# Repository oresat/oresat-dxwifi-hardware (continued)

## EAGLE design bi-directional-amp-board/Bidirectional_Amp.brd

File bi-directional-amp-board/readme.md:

Notes on the Bi-Directional DxWiFi (2.412 GHz) Amp PCB
========================================================

Our stackup is something like this:

 1.2 mil - 1 oz Copper
13.3 mil - Rogers RO4350B
 1.2 mil - 1 oz Copper
31.1 mil - FR4 (e.g., NP175)
 1.2 mil - 1 oz Copper
13.3 mil - Rogers RO4350B
 1.2 mil - 1 oz Copper
--------
62.5 mil - 1/16" standard board thickness

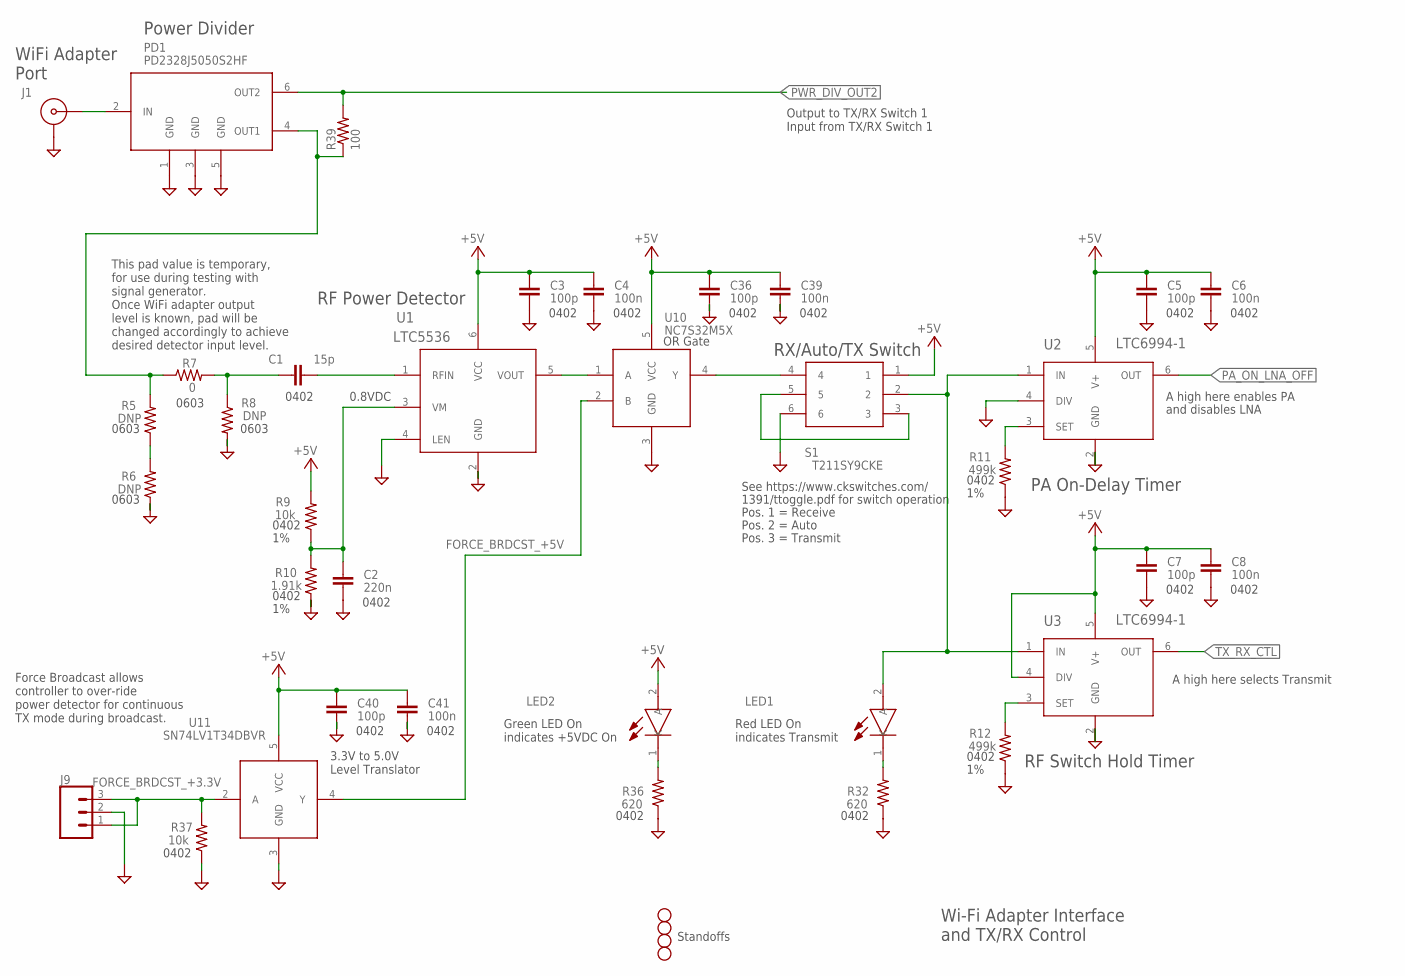
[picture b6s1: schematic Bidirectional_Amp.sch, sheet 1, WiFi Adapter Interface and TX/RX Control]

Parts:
C1: 15p; .0402-B-NOSILK; MPN GJM1555C1H150JB01D
C2: 220n; .0402-B-NOSILK; MPN C1005X7R1C224K050BE
C3, C5, C7, C36, C40: 100p; .0402-B-NOSILK; MPN GCM1555C1H101JA16D
C4, C6, C8, C39, C41: 100n; .0402-B-NOSILK; MPN CGA2B1X7R1C104K050BC
H1, H2, H3, H4: STAND-OFFTIGHT; STAND-OFF-TIGHT
J1: 73415-2061; 73415-2063; MPN 0734152061
J9: CONN_03LONGPADS; 1X03_LONGPADS
LED1: LTST-C193KRKT-5A; LEDC1607X80N
LED2: LTST-C193KGKT-5A; LEDC1607X80N
PD1: PD2328J5050S2HF; PSON65P204X129X58-6N
R5, R6, R8: DNP; R0603
R7: 0; R0603; MPN ERJ-3GEY0R00V
R9: 10k; .0402-B-NOSILK; MPN ERJ-2RKF1002X
R10: 1.91k; .0402-B-NOSILK; MPN ERJ-2RKF1911X
R11, R12: 499k; .0402-B-NOSILK; MPN ERJ-2RKF4993X
R32, R36: 620; .0402-B-NOSILK; MPN ERJ-2GEJ621X
R37: 10k; .0402-B-NOSILK; MPN ERJ-2GEJ103X
R39: 100; .0603-C-NOSILK; MPN ERJ-3EKF1000V
S1: T211SY9CKE; T201MH9V3BE
U1: LTC5536; TSOT-23_S6
U2, U3: LTC6994-1; TSOT-23_S6
U10: NC7S32M5X; SOT95P280X145-5N
U11: SN74LV1T34DBVR; SOT95P280X145-5N

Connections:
+5V: C3.1, C4.1, C5.1, C6.1, C7.1, C8.1, C36.1, C39.1, C40.1, C41.1, LED2.2 (A), R9.2, S1.1, U1.6 (VCC), U2.5 (V+), U3.4 (DIV), U3.5 (V+), U10.5 (VCC), U11.5 (VCC); also elsewhere on the board
FORCE_BRDCST_+3.3V: J9.1, J9.3, R37.2, U11.2 (A)
FORCE_BRDCST_+5V: U10.2 (B), U11.4 (Y)
GND: C2.2, C3.2, C4.2, C5.2, C6.2, C7.2, C8.2, C36.2, C39.2, C40.2, C41.2, J1.2 (GND), J1.3 (GND), J1.4 (GND), J1.5 (GND), J9.2, PD1.1 (GND), PD1.3 (GND), PD1.5 (GND), R6.1, R8.2, R10.1, R11.1, R12.1, R32.1, R36.1, R37.1, S1.6, U1.2 (GND), U1.4 (LEN), U2.2 (GND), U2.4 (DIV), U3.2 (GND), U10.3 (GND), U11.3 (GND); also elsewhere on the board
unnamed: J1.1 (CTR), PD1.2 (IN)
unnamed: U1.5 (VOUT), U10.1 (A)
unnamed: PD1.4 (OUT1), R5.2, R7.1, R39.1
unnamed: C1.1, R7.2, R8.1
unnamed: R5.1, R6.2
unnamed: C1.2, U1.1 (RFIN)
unnamed: C2.1, R9.1, R10.2, U1.3 (VM)
unnamed: LED1.2 (A), S1.2, U2.1 (IN), U3.1 (IN)
unnamed: R11.2, U2.3 (SET)
unnamed: S1.3, S1.5
unnamed: R12.2, U3.3 (SET)
unnamed: LED1.1 (K), R32.2
unnamed: LED2.1 (K), R36.2
unnamed: S1.4, U10.4 (Y)
PA_ON_LNA_OFF: U2.6 (OUT); also elsewhere on the board
PWR_DIV_OUT2: PD1.6 (OUT2), R39.2; also elsewhere on the board
TX_RX_CTL: U3.6 (OUT); also elsewhere on the board

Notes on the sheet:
0603
0402
0.8VDC
RF Power Detector
Power Divider
PA On-Delay Timer
RF Switch Hold Timer
RX/Auto/TX Switch
See https://www.ckswitches.com/
1391/ttoggle.pdf for switch operation
Pos. 1 = Receive
Pos. 2 = Auto
Pos. 3 = Transmit
A high here enables PA
and disables LNA
A high here selects Transmit
Force Broadcast allows controller to over-ride power detector for continuous TX mode during broadcast.
WiFi Adapter Port
Wi-Fi Adapter Interface and TX/RX Control
Red LED On indicates Transmit
Green LED On indicates +5VDC On
OR Gate
3.3V to 5.0V Level Translator
This pad value is temporary, for use during testing with signal generator. Once WiFi adapter output level is known, pad will be changed accordingly to achieve desired detector input level.
Standoffs
Output to TX/RX Switch 1 Input from TX/RX Switch 1

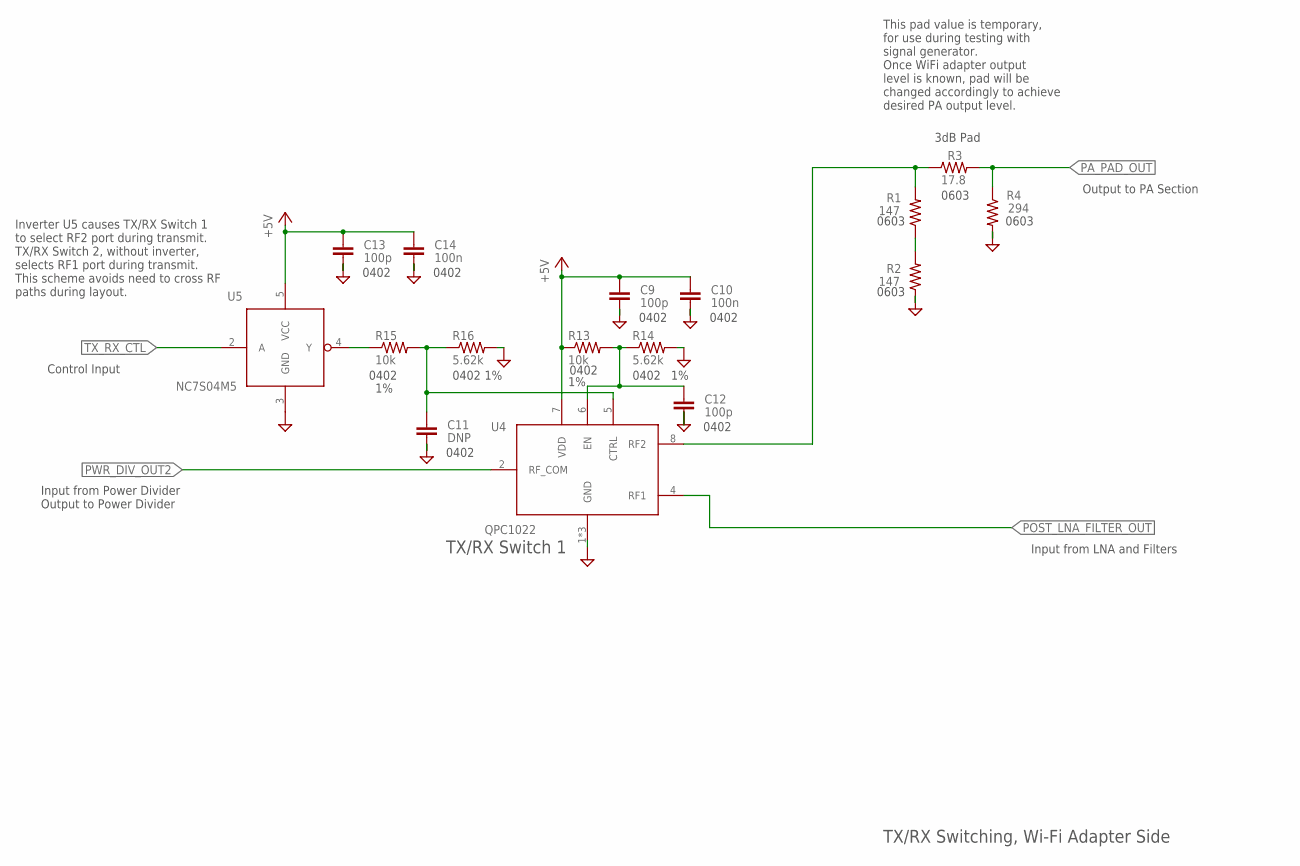
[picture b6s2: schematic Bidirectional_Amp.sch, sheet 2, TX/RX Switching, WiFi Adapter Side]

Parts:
C9, C12, C13: 100p; .0402-B-NOSILK; MPN GCM1555C1H101JA16D
C10, C14: 100n; .0402-B-NOSILK; MPN CGA2B1X7R1C104K050BC
C11: DNP; .0402-B-NOSILK; MPN GCM1555C1H101JA16D
R1, R2: 147; R0603; MPN ERJ-3EKF1470V
R3: 17.8; R0603; MPN ERJ-3EKF17R8V
R4: 294; R0603; MPN ERJ-3EKF2940V
R13, R15: 10k; .0402-B-NOSILK; MPN ERJ-2RKF1002X
R14, R16: 5.62k; .0402-B-NOSILK; MPN ERJ-2RKF5621X
U4: QPC1022; MPN QPC1022SR
U5: NC7S04M5; SOT95P280X140-5N

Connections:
+5V: C9.1, C10.1, C13.1, C14.1, R13.1, U4.7 (VDD), U5.5 (VCC); also elsewhere on the board
GND: C9.2, C10.2, C11.2, C12.2, C13.2, C14.2, R2.1, R4.2, R14.2, R16.2, U4.1 (GND), U4.3 (GND), U4.9 (GND), U5.3 (GND); also elsewhere on the board
unnamed: R1.2, R3.1, U4.8 (RF2)
unnamed: R1.1, R2.2
unnamed: C12.1, R13.2, R14.1, U4.6 (EN)
unnamed: C11.1, R15.2, R16.1, U4.5 (CTRL)
unnamed: R15.1, U5.4 (Y)
PA_PAD_OUT: R3.2, R4.1; also elsewhere on the board
POST_LNA_FILTER_OUT: U4.4 (RF1); also elsewhere on the board
PWR_DIV_OUT2: U4.2 (RF_COM); also elsewhere on the board
TX_RX_CTL: U5.2 (A); also elsewhere on the board

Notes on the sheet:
3dB Pad
0603
0402
TX/RX Switch 1
Inverter U5 causes TX/RX Switch 1 to select RF2 port during transmit. TX/RX Switch 2, without inverter, selects RF1 port during transmit. This scheme avoids need to cross RF paths during layout.
This pad value is temporary, for use during testing with signal generator. Once WiFi adapter output level is known, pad will be changed accordingly to achieve desired PA output level.
TX/RX Switching, Wi-Fi Adapter Side
Output to PA Section
Input from LNA and Filters
Input from Power Divider Output to Power Divider
Control Input

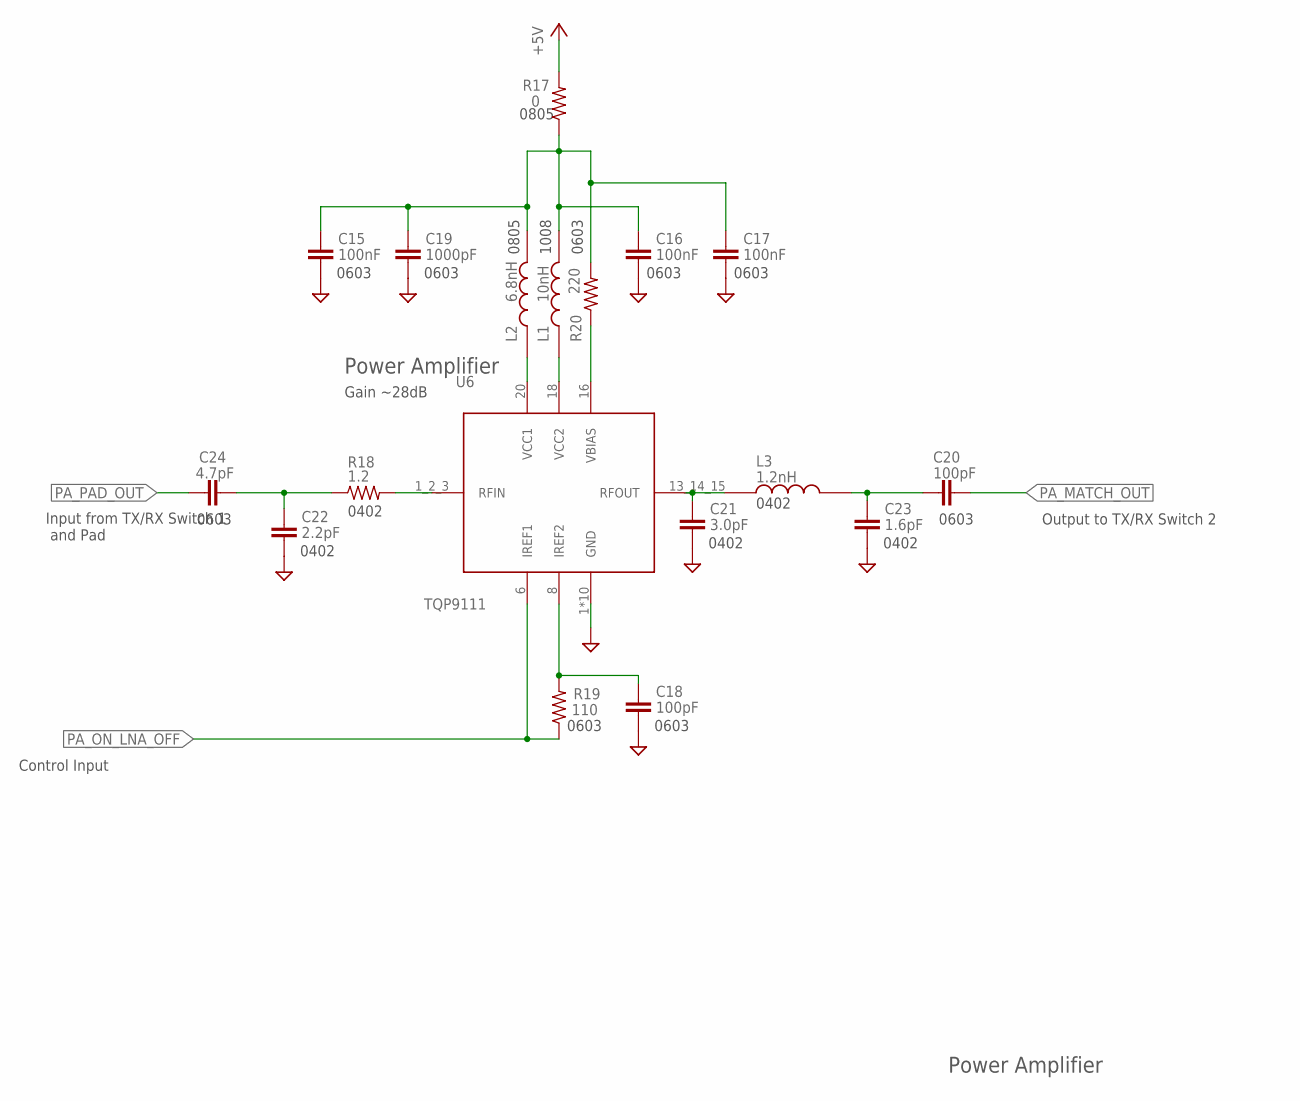
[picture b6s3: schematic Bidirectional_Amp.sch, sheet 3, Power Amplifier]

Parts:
C15, C16, C17: 100nF; C0603; MPN C0603C104K5RACAUTO
C18, C20: 100pF; C0603; MPN GCM1885C1H101JA16D
C19: 1000pF; C0603; MPN CGA3E2C0G1H102J080AA
C21: 3.0pF; C0402; MPN UVK105CG030JW-F
C22: 2.2pF; C0402; MPN UVK105CG2R2JW-F
C23: 1.6pF; C0402; MPN GJM1555C1H1R6BB01D
C24: 4.7pF; C0603; MPN 06032U4R7BAT2A
L1: 10nH; INDC2928X203N
L2: 6.8nH; 0805CS
L3: 1.2nH; 0402CS1N2XJLW
R17: 0; R0805; MPN ERJ-6GEY0R00V
R18: 1.2; R0402; MPN ERJ-2GEJ1R2X
R19: 110; R0603; MPN ERJ-3EKF1100V
R20: 220; R0603; MPN ERJ-3EKF2200V
U6: TQP9111; SAMACSYS_PARTS_QFN50P400X400X102-21N

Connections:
+5V: R17.2; also elsewhere on the board
GND: C15.2, C16.2, C17.2, C18.2, C19.2, C21.2, C22.2, C23.2, U6.1 (GND), U6.5 (GND), U6.7 (GND), U6.9 (GND), U6.10 (GND), U6.11 (GND), U6.15 (GND), U6.17 (GND), U6.19 (GND), U6.21 (GND); also elsewhere on the board
unnamed: R20.1, U6.16 (VBIAS)
unnamed: L1.1, U6.18 (VCC2)
unnamed: L2.1, U6.20 (VCC1)
unnamed: C15.1, C16.1, C17.1, C19.1, L1.2, L2.2, R17.1, R20.2
unnamed: C18.1, R19.2, U6.8 (IREF2)
unnamed: C21.1, L3.1, U6.13_14_15 (RFOUT)
unnamed: C22.1, C24.2, R18.1
unnamed: C20.1, C23.1, L3.2
unnamed: R18.2, U6.1_2_3 (RFIN)
PA_MATCH_OUT: C20.2; also elsewhere on the board
PA_ON_LNA_OFF: R19.1, U6.6 (IREF1); also elsewhere on the board
PA_PAD_OUT: C24.1; also elsewhere on the board

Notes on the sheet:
0603
0402
1008
0805
Power Amplifier
Output to TX/RX Switch 2
Control Input
Input from TX/RX Switch 1 and Pad
Gain ~28dB

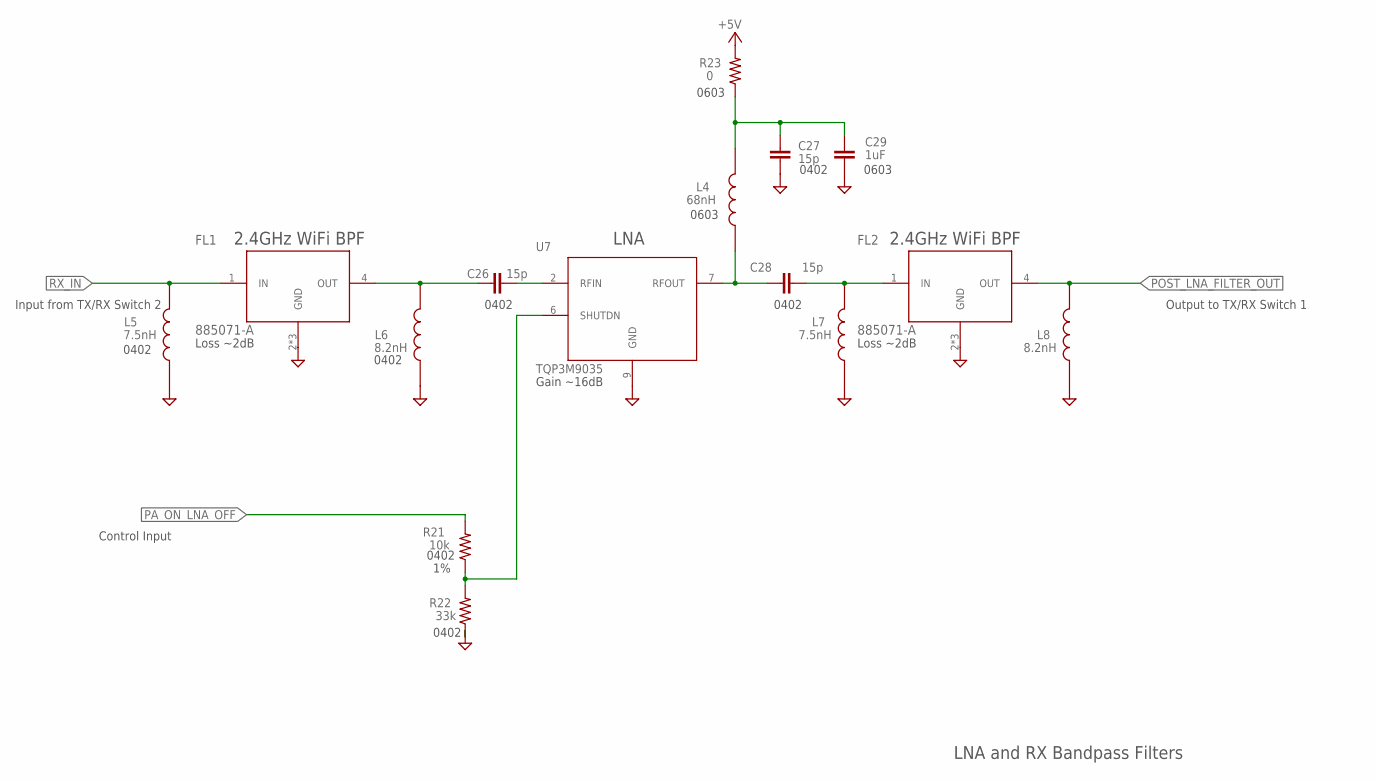
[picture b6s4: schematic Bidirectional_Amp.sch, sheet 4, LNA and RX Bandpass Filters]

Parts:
C26, C28: 15p; C0402; MPN GJM1555C1H150JB01D
C27: 15p; .0402-B-NOSILK; MPN GJM1555C1H150JB01D
C29: 1uF; C0603; MPN C0603X105M4RACAUTO
FL1, FL2: 885071-A; FIL_B39162B9417K610; MPN 885071-A
L4: 68nH; 0603CS-68NXJLW
L5, L7: 7.5nH; 0402CS1N2XJLW; MPN 0402CS-7N5XGLU
L6, L8: 8.2nH; 0402CS1N2XJLW; MPN 0402CS-8N2XGLU
R21: 10k; .0402-B-NOSILK; MPN ERJ-2RKF1002X
R22: 33k; .0402-B-NOSILK; MPN ERJ-2GEJ333X
R23: 0; R0603; MPN ERJ-3GEY0R00V
U7: TQP3M9035; DFN-8; MPN TQP3M9035

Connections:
+5V: R23.2; also elsewhere on the board
GND: C27.1, C29.2, FL1.2 (GND), FL1.3 (GND), FL1.5 (GND), FL2.2 (GND), FL2.3 (GND), FL2.5 (GND), L5.1, L6.1, L7.1, L8.1, R22.1, U7.9 (GND); also elsewhere on the board
unnamed: C26.2, U7.2 (RFIN)
unnamed: C28.1, L4.1, U7.7 (RFOUT)
unnamed: C27.2, C29.1, L4.2, R23.1
unnamed: R21.1, R22.2, U7.6 (SHUTDN)
unnamed: C26.1, FL1.4 (OUT), L6.2
unnamed: C28.2, FL2.1 (IN), L7.2
PA_ON_LNA_OFF: R21.2; also elsewhere on the board
POST_LNA_FILTER_OUT: FL2.4 (OUT), L8.2; also elsewhere on the board
RX_IN: FL1.1 (IN), L5.2; also elsewhere on the board

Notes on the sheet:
0402
0603
LNA
2.4GHz WiFi BPF
LNA and RX Bandpass Filters
Input from TX/RX Switch 2
Control Input
Output to TX/RX Switch 1
Gain ~16dB
Loss ~2dB

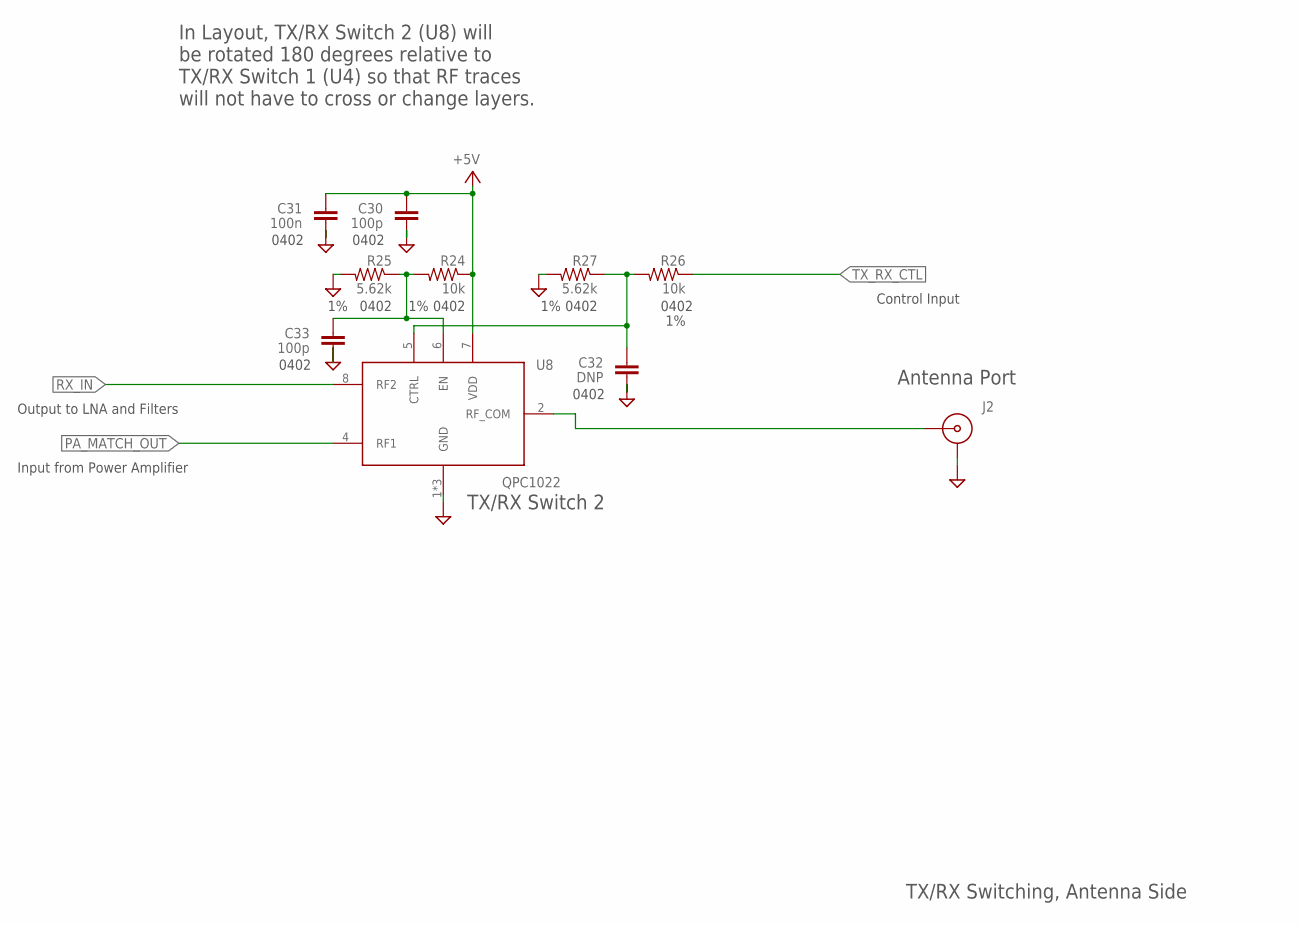
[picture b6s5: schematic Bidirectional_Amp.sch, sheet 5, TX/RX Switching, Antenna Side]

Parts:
C30, C33: 100p; .0402-B-NOSILK; MPN GCM1555C1H101JA16D
C31: 100n; .0402-B-NOSILK; MPN CGA2B1X7R1C104K050BC
C32: DNP; .0402-B-NOSILK; MPN GCM1555C1H101JA16D
J2: 73415-2061; 73415-2063
R24, R26: 10k; .0402-B-NOSILK; MPN ERJ-2RKF1002X
R25, R27: 5.62k; .0402-B-NOSILK; MPN ERJ-2RKF5621X
U8: QPC1022

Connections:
+5V: C30.1, C31.1, R24.1, U8.7 (VDD); also elsewhere on the board
GND: C30.2, C31.2, C32.2, C33.2, J2.2 (GND), J2.3 (GND), J2.4 (GND), J2.5 (GND), R25.2, R27.2, U8.1 (GND), U8.3 (GND), U8.9 (GND); also elsewhere on the board
unnamed: J2.1 (CTR), U8.2 (RF_COM)
unnamed: C33.1, R24.2, R25.1, U8.6 (EN)
unnamed: C32.1, R26.2, R27.1, U8.5 (CTRL)
PA_MATCH_OUT: U8.4 (RF1); also elsewhere on the board
RX_IN: U8.8 (RF2); also elsewhere on the board
TX_RX_CTL: R26.1; also elsewhere on the board

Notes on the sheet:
0402
TX/RX Switch 2
Antenna Port
TX/RX Switching, Antenna Side
In Layout, TX/RX Switch 2 (U8) will be rotated 180 degrees relative to TX/RX Switch 1 (U4) so that RF traces will not have to cross or change layers.
Input from Power Amplifier
Output to LNA and Filters
Control Input

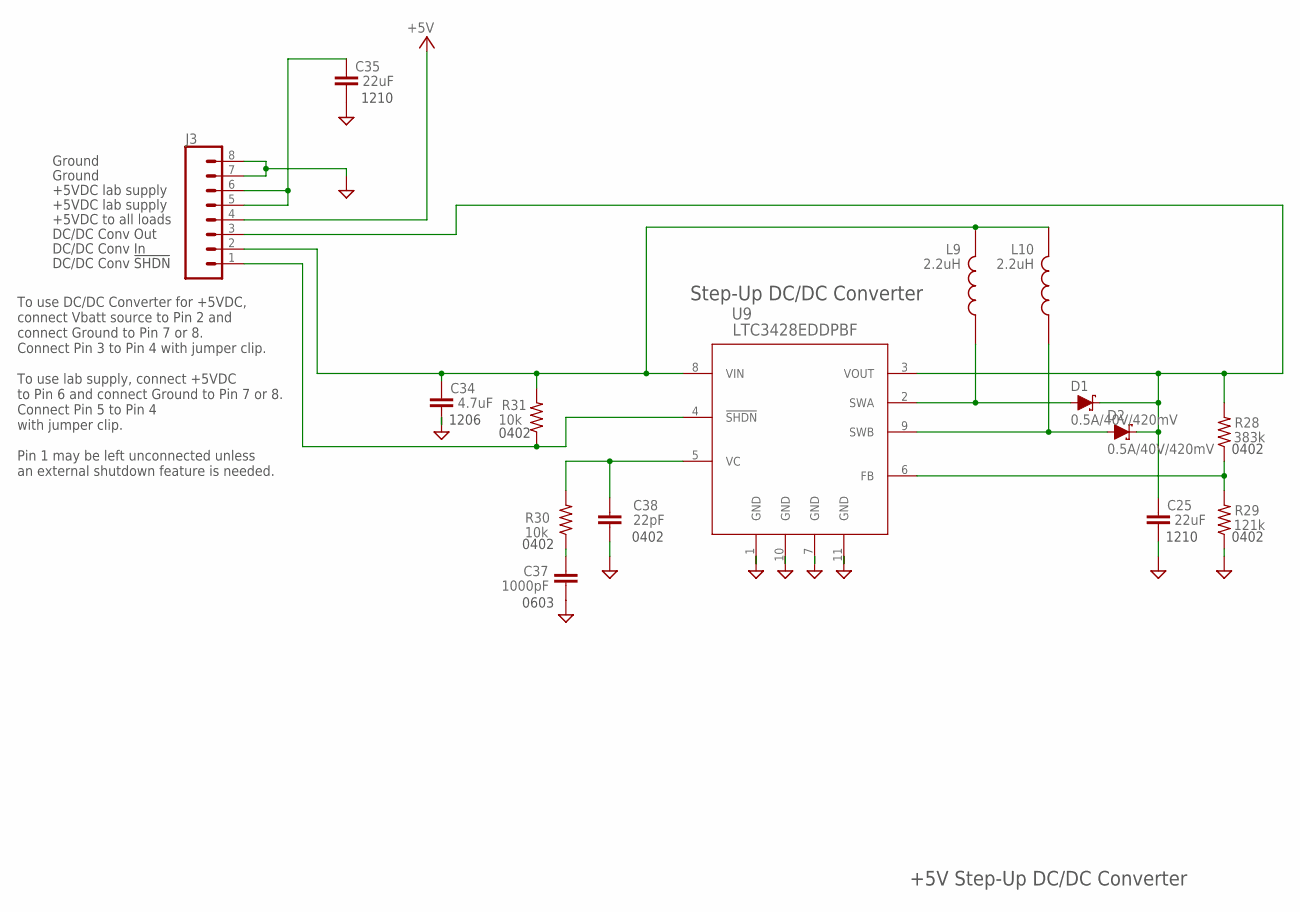
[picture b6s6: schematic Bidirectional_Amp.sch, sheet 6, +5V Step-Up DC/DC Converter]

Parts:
C25, C35: 22uF; C1210; MPN GCJ32ER71C226KE01L
C34: 4.7uF; C1206; VOLTAGE 16V; MPN GCJ31CR71C475KA01L
C37: 1000pF; C0603; MPN CGA3E2C0G1H102J080AA
C38: 22pF; .0402-B-NOSILK; MPN GCM1555C1H220JA16J
D1, D2: 0.5A/40V/420mV; SOD-323; MPN PMEG1020EJ,115
J3: CONN_08LONGPADS; 1X08_LONGPADS
L9, L10: 2.2uH; XFL4020-222ME
R28: 383k; .0402-B-NOSILK; MPN ERJ-2RKF3833X
R29: 121k; .0402-B-NOSILK; MPN ERJ-2RKF1213X
R30: 10k; .0402-B-NOSILK; MPN ERJ-2RKF1002X
R31: 10k; .0402-B-NOSILK; MPN ERJ-2GEJ103X
U9: LTC3428EDDPBF; DFN-10_DD

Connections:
+5V: J3.4; also elsewhere on the board
FB1: R28.1, R29.2, U9.6 (FB)
GND: C25.2, C34.2, C35.2, C37.2, C38.2, J3.7, J3.8, R29.1, U9.1 (GND), U9.7 (GND), U9.10 (GND), U9.11 (GND); also elsewhere on the board
unnamed: C37.1, R30.1
unnamed: C35.1, J3.5, J3.6
SHDN1: J3.1, R31.1, U9.4 (!SHDN)
SWA1: D1.A, L9.1, U9.2 (SWA)
SWB1: D2.A, L10.1, U9.9 (SWB)
VC1: C38.1, R30.2, U9.5 (VC)
VIN1: C34.1, J3.2, L9.2, L10.2, R31.2, U9.8 (VIN)
VOUT1: C25.1, D1.C, D2.C, J3.3, R28.2, U9.3 (VOUT)

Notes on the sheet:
+5V Step-Up DC/DC Converter
1206
1210
0603
0402
+5VDC lab supply
+5VDC to all loads
DC/DC Conv Out
DC/DC Conv In
DC/DC Conv !SHDN!
To use DC/DC Converter for +5VDC, connect Vbatt source to Pin 2 and connect Ground to Pin 7 or 8. Connect Pin 3 to Pin 4 with jumper clip. To use lab supply, connect +5VDC to Pin 6 and connect Ground to Pin 7 or 8. Connect Pin 5 to Pin 4 with jumper clip. Pin 1 may be left unconnected unless an ext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
Step-Up DC/DC Converter
Ground

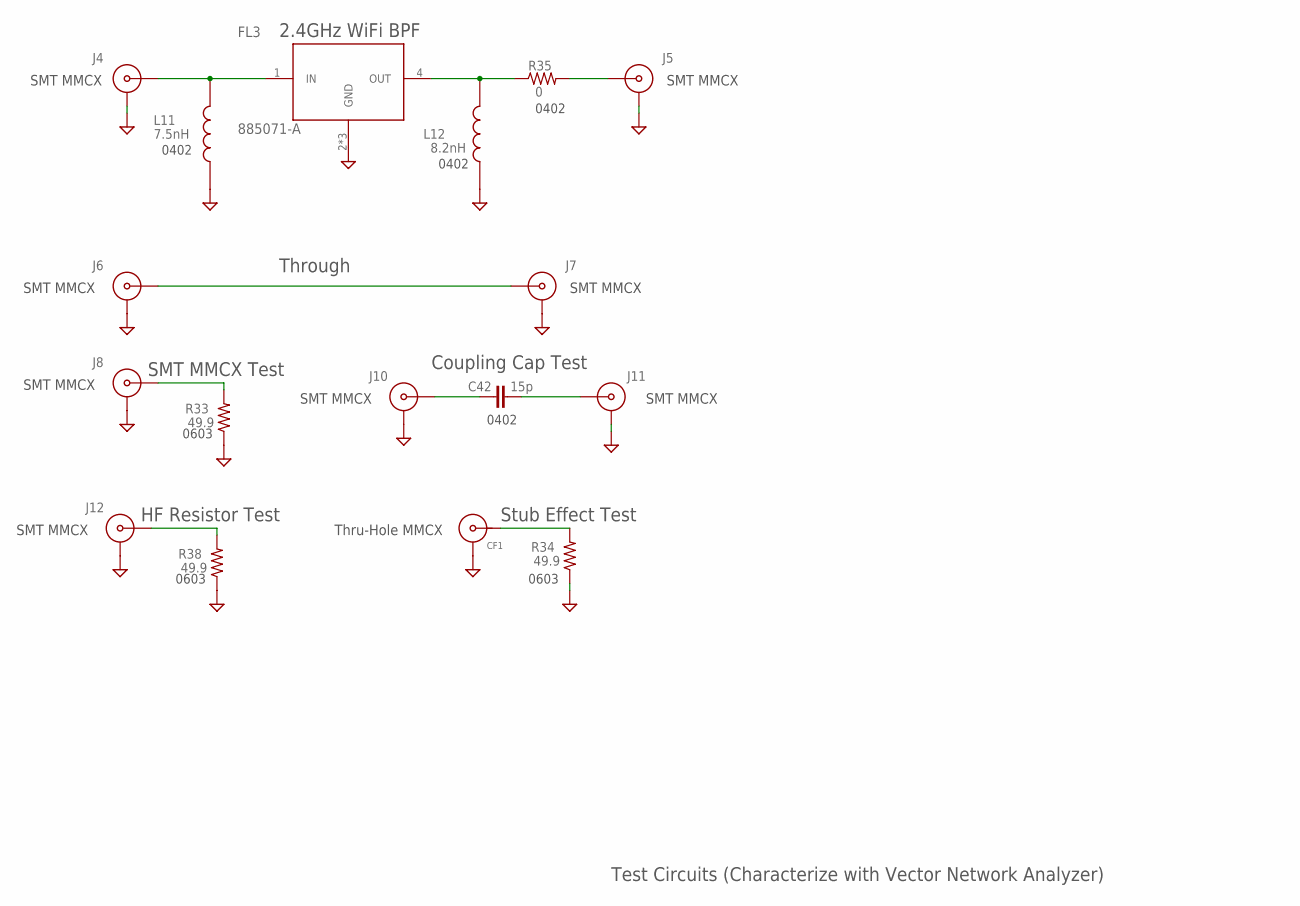
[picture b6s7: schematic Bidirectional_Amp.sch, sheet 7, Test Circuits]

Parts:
C42: 15p; .0402-B-NOSILK; MPN GJM1555C1H150JB01D
CF1: CON-MMCX-F-MOLEX-0734151001; MPN 0734151001
FL3: 885071-A; FIL_B39162B9417K610; MPN 885071-A
J4, J5, J6, J7, J8, J10, J11, J12: 73415-2061; 73415-2063
L11: 7.5nH; 0402CS1N2XJLW; MPN 0402CS-7N5XGLU
L12: 8.2nH; 0402CS1N2XJLW; MPN 0402CS-8N2XGLU
R33, R34: 49.9; R0603; MPN ERJ-3EKF49R9V
R35: 0; .0402-B-NOSILK; MPN ERJ-2GE0R00X
R38: 49.9; R0603; MPN MCT06030C4999FP500

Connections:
GND: CF1.G1 (SHIELD), CF1.G2 (SHIELD), CF1.G3 (SHIELD), CF1.G4 (SHIELD), FL3.2 (GND), FL3.3 (GND), FL3.5 (GND), J4.2 (GND), J4.3 (GND), J4.4 (GND), J4.5 (GND), J5.2 (GND), J5.3 (GND), J5.4 (GND), J5.5 (GND), J6.2 (GND), J6.3 (GND), J6.4 (GND), J6.5 (GND), J7.2 (GND), J7.3 (GND), J7.4 (GND), J7.5 (GND), J8.2 (GND), J8.3 (GND), J8.4 (GND), J8.5 (GND), J10.2 (GND), J10.3 (GND), J10.4 (GND), J10.5 (GND), J11.2 (GND), J11.3 (GND), J11.4 (GND), J11.5 (GND), J12.2 (GND), J12.3 (GND), J12.4 (GND), J12.5 (GND), L11.1, L12.1, R33.1, R34.1, R38.1; also elsewhere on the board
unnamed: FL3.4 (OUT), L12.2, R35.1
unnamed: FL3.1 (IN), J4.1 (CTR), L11.2
unnamed: J6.1 (CTR), J7.1 (CTR)
unnamed: J8.1 (CTR), R33.2
unnamed: CF1.CENTER, R34.2
unnamed: J5.1 (CTR), R35.2
unnamed: C42.1, J10.1 (CTR)
unnamed: C42.2, J11.1 (CTR)
unnamed: J12.1 (CTR), R38.2

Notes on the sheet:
Test Circuits (Characterize with Vector Network Analyzer)
2.4GHz WiFi BPF
Through
SMT MMCX
Thru-Hole MMCX
0603
0402
Coupling Cap Test
HF Resistor Test
Stub Effect Test
SMT MMCX Test

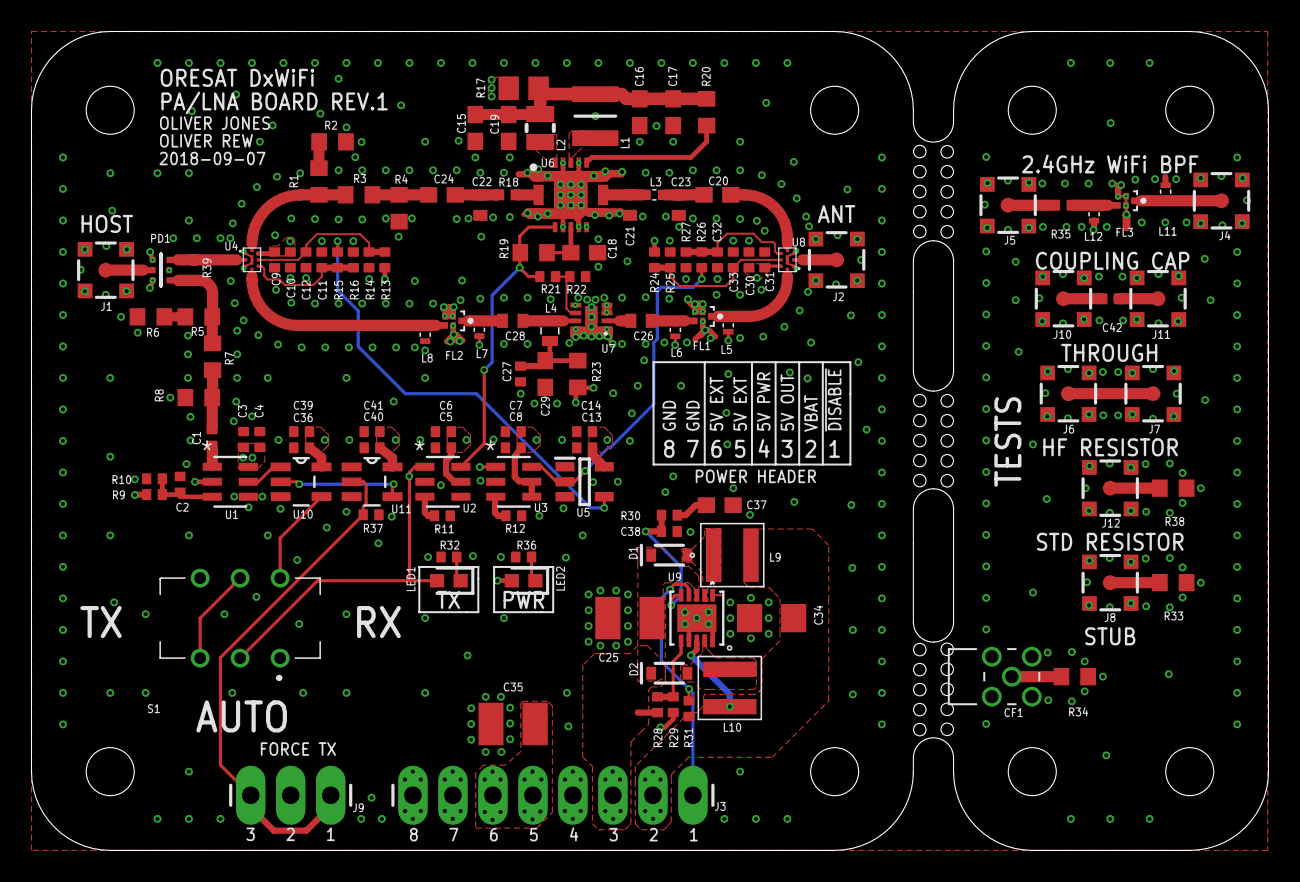
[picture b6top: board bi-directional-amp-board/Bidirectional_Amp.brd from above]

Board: 4 copper layers, 78.5 x 52.0 mm, 134 parts (0 on the bottom side), 66 nets.

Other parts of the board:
H5, H6, H7, H8: STAND-OFFTIGHT; STAND-OFF-TIGHT@1

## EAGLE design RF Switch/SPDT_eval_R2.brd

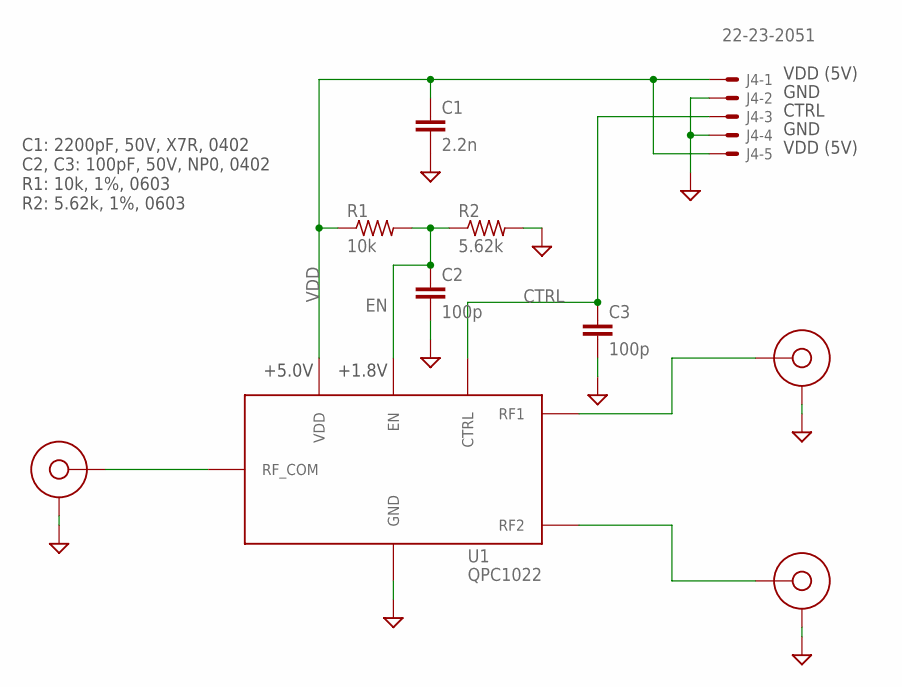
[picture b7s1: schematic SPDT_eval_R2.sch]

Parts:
C1: 2.2n; .0402-B-NOSILK
C2, C3: 100p; .0402-B-NOSILK
CF1, CF2, CF3: SMA-CINCH-END-FIRE; SMAJ716-ND
J4: 22-23-2051
R1: 10k; .0603-B-NOSILK
R2: 5.62k; .0603-B-NOSILK
U1: QPC1022

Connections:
COM: CF1.P$3 (CENTERCONDUCTOR), U1.ANT (RF_COM)
CTRL: C3.1, J4.3, U1.CTRL
EN: C2.1, R1.2, R2.1, U1.EN
GND: C1.2, C2.2, C3.2, CF1.GND1 (GND), CF1.GND2 (GND), CF1.GND3 (GND), CF1.GND4 (GND), CF2.GND1 (GND), CF2.GND2 (GND), CF2.GND3 (GND), CF2.GND4 (GND), CF3.GND1 (GND), CF3.GND2 (GND), CF3.GND3 (GND), CF3.GND4 (GND), J4.2, J4.4, R2.2, U1.GND@1 (GND), U1.GND@2 (GND), U1.GND@3 (GND); also elsewhere on the board
RF1: CF2.P$3 (CENTERCONDUCTOR), U1.RF1
RF2: CF3.P$3 (CENTERCONDUCTOR), U1.RF2
VDD: C1.1, J4.1, J4.5, R1.1, U1.VDD; also elsewhere on the board

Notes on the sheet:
C1: 2200pF, 50V, X7R, 0402 C2, C3: 100pF, 50V, NP0, 0402 R1: 10k, 1%, 0603 R2: 5.62k, 1%, 0603
+5.0V
+1.8V
VDD (5V)
GND
CTRL

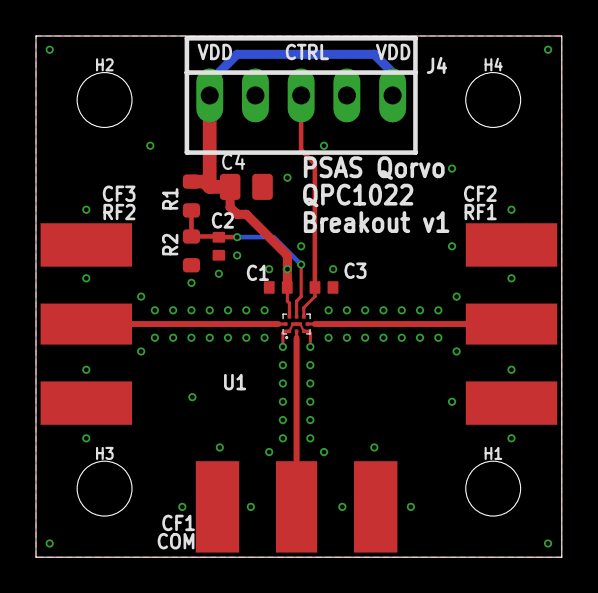
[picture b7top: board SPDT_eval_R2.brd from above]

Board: 4 copper layers, 29.2 x 29.0 mm, 15 parts (0 on the bottom side), 7 nets.

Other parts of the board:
C4: 10u; .0805-B-NOSILK
H1, H2, H3, H4: STAND-OFFTIGHT; STAND-OFF-TIGHT

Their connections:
GND: C4.2; also elsewhere on the board
VDD: C4.1; also elsewhere on the board

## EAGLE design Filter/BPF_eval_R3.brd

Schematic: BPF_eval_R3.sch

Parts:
CF1, CF2, CF3, CF4: SMA-CINCH-END-FIRE; SMAJ716-ND
H1, H2: STAND-OFFTIGHT; STAND-OFF-TIGHT
L1: 7.5nH; .0402-B-NOSILK
L2: 8.2nH; .0402-B-NOSILK
U1: 885071-A; FIL_B39162B9417K610

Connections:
GND: CF1.GND1 (GND), CF1.GND2 (GND), CF1.GND3 (GND), CF1.GND4 (GND), CF2.GND1 (GND), CF2.GND2 (GND), CF2.GND3 (GND), CF2.GND4 (GND), CF3.GND1 (GND), CF3.GND2 (GND), CF3.GND3 (GND), CF3.GND4 (GND), CF4.GND1 (GND), CF4.GND2 (GND), CF4.GND3 (GND), CF4.GND4 (GND), L1.2, L2.2, U1.2 (GND), U1.3 (GND), U1.5 (GND)
IN: CF1.P$3 (CENTERCONDUCTOR), L1.1, U1.1 (IN)
OUT: CF3.P$3 (CENTERCONDUCTOR), L2.1, U1.4 (OUT)
THROUGH: CF2.P$3 (CENTERCONDUCTOR), CF4.P$3 (CENTERCONDUCTOR)

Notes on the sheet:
0402
Qorvo 885071-A
Through
Standoffs

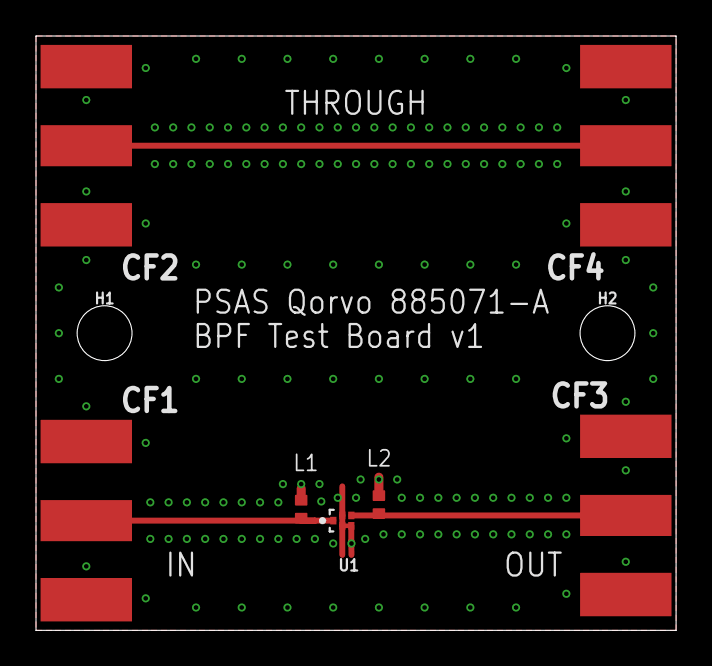
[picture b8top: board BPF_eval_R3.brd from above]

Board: 4 copper layers, 35.6 x 33.0 mm, 9 parts (0 on the bottom side), 4 nets.

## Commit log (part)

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2018-08-11 you know the drill
2018-08-11 layed out the boost converter
2018-08-12 getting close
2018-08-14 minor fixes
2018-08-29 mawr
2018-09-06 a few updates
2018-09-07 more refinements
2018-09-08 changes from design review
2018-11-15 added v1 revision notes
2019-01-30 Initial link model
    Antenna gains at 16dBi. Ground station antenna noise temperature is unknown; needs measurement. Transmitters set to 2W. Transmitter and receiver details are estimates. Modulation set to BPSK w/o FEC 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
2019-01-31 Notes fix
2019-02-01 Customized transmitters and receivers templates
2019-02-01 changed stencil openings per request
2019-02-11 This is now the hardware repo only.
2019-02-11 Better formatting, links.
2019-03-27 Added first version of the AR9271 evaluation board. No board layou yet.
2019-04-19 Most up to date board
2019-05-06 BRD and SCH now back in sync
2019-05-27 Updated link models
2019-05-28 Updated mod/demod to include FEC
2019-06-21 Updates after design review.
2019-07-15 Update UniClOGS to match handheld
2019-09-10 Update receivers and spreadsheet formatting
2019-09-11 Handheld link model formatting, minor fixes, update handheld antenna
2019-09-16 First pass of the updated AR9271 dev board. Took Stephen's fine board, and OCD'd it. Still requires stiching, better LAYER3 power layout, TNAMES cleanup, better stiching, but it's close!
2019-09-16 More stitching, polishing of power layer, no ERCs or DRCs.
2019-09-17 Rename - delete link models
2019-09-17 Rename - new link model names
2019-09-17 whoops
2019-09-18 Added holes for feet, more stitching, and DRC cleanup. DONE! SHIP IT!
2019-10-25 Added V2 board with separate TX and RX interfaces to WiFi chip
2019-11-09 Fixed silk screen based on Jeff's feedback. No change to layout, so same version.
2019-11-17 Check in for Vigely to do some modeling. All routed, but not yet polished.
2019-11-19 Cleanup, suggested by Oliver(s).
2019-12-01 Made the LNAs the correct part number.
2020-03-07 New PA test board, follows better RF practices, new input matching network, and some pointers from Qorvo.
2020-03-09 Cleaned up DRCs and stiching.
2020-03-11 Fixed filename.
2020-10-08 Added 1st draft layout for Oliver
2020-10-25 Final tweaks to the V2 after getting the V1 to work!
2021-01-13 Removed star tracker traces and added dxwifiboard.dxf
2021-01-19 placed components in proposed locations
2021-01-21 Third time is the charm? Started with Star Tracker v1.2, added new card outline, moved out all extraneaous stuff, added RF connectors.
2021-01-22 Moved components to clear the camera
2021-01-24 Routed emmc without impedance matching
2021-01-24 reverted impedance matching
2021-01-24 Routed emmc lines
2021-01-24 conected the emms to the octavo
2021-01-25 routed R26 array
2021-01-26 routed jtag and CAN transceiver uart
2021-01-26 fixed incorrect trace widths
2021-01-26 Removed unused jumpers left over from star tracker
2021-01-27 routed power for wifi
2021-01-27 Updated to tuned values, fixed BOM formatting.
2021-01-29 rerouted USB on top layer and conected it to the wifi conector
2021-01-30 got most signals off layer 15
2021-02-02 Fixed WF connector pinout
2021-02-02 Got the SD card traces off layer 15
2021-02-02 Moved OPD power indicator LEDs out of the way for RF
2021-02-03 Rearanged the front right to make more room for the WF 5v regulator
2021-02-04 routed the 5V supply for the PA and placed it on the board in a temporary spot
2021-02-04 added schematic sheet for RF
2021-02-06 Added the PA design block
2021-02-09 Moved the WiFi module to the bottom and rerouted the PA 5V regulator
2021-02-11 Added a thermister for the PA following the C3 implementation
2021-02-11 added vias to all 3.3v conections for a 3.3v pour on layer 15
2021-02-12 Added the status LED and power toggole resistor for the WiFi module
2021-02-14 chose gpio3_9 for PA_ENABLE
2021-02-15 fixed routing errors
2021-02-17 moved the PA 5V supply to the top right of the board and routed the PA TX connections
2021-02-18 routed 5V connections and cleaned up airwires and missing ground connections
2021-02-18 Removed the thermal designation from nessicary polygon pours
2021-02-19 Added 5V_PA polygon, did some OCD cleanup on RF sheet, yelled at Nick a lot.
2021-02-19 modified thermistor routing to not go though vias after it was moved
2021-02-19 Added a silkscreen identifier for the PA enable LED
2021-02-20 reworked the 5V and 3.3V polygon routing
2021-02-21 length matched the emmc data lines
2021-02-21 Added ground vias next to the RF inductors, SMPM connector, and more around the U.FL
2021-02-21 Verified all component keepout errors for adequate soldermask clerance and move a few
2021-02-21 Cleared the PA thermal path
2021-02-22 placed the silkscreen elements
2021-02-22 Added attributes to all green LEDs
2021-02-28 Added 2 more vias to the thermal path
2021-03-08 Small fixes; polishing.
2021-04-05 Updated board text to v1.1, updated flight hardware marker, fixed eMMC routed through A6 issue
2021-04-05 Moved R22 to uncover the octavo pin 1 deginator
2021-04-05 Made a small change to the RF tStop at L7
2021-04-05 Updated the OR gate and the high side PA enable footprints
2021-04-09 Adjusted misc silkscreen labels and corrected connector refdes's
2021-04-12 Replaced all test points for the PA support circuits with through hole test points
2021-04-12 changed the date on the PCB
2021-04-19 Changed TP1 on the VOUT_USB to a through hole insted of a pad
2021-04-19 Fixed the WF sourcing power from 2 sources and increased all 3.3V and 5V led resistors
2021-05-22 Added revised BOM and pdf of latest schematic
2021-08-04 added crystal for the USB hub
2021-08-04 added usb hub reset pullup and vcc filter cap
2021-08-05 Made progress on adding the USB hub and power switches
2021-08-06 replaced boot and PA_enable jumpres with smaller one, started clearing space for the usb hub
2021-08-07 added Oliver J's name and organized the ratsnest components off the board
2021-08-07 changed camera connector pinout to match wifi
2021-08-07 placed hub and usb data line componants
2021-08-07 mid way placing crystal
2021-08-08 routed data and power for host and wifi
2021-08-08 routed forgotten 5V for camera power
2021-08-08 added copper pour around adjcent 3.3v pads on the hub
2021-08-08 Made all chnges discused in 8/8 design review
2021-08-08 placed sysboot instructions and ran DRC
2021-08-09 added u.fl passthrough hole
2021-08-09 Final polish on v1.1.
    - Added pulldowns on unused USB port, added pullup on !OC input for that port.
    - Added TPL/BPL lines for the camera board and lens holder. Moved some parts around to avoid the 33.5 mm OD of the lens holder.
    - TNAMES cleanup
    - Made some traces thicker (don't use TRACE rule for wires if you can help it)
    - Fixed isolate on some layer 15 polygons
    - Cleaned up some traces coming non-orthogonally out of pads.
2021-08-15 cleaned up the schamatic and added notes for the new usb connections
2021-08-15 cleaned up most DRC errors
2021-08-15 updated BOM to include new USB hub components
2021-08-15 removed out of date schematics and BOMs
2021-08-28 started ripping things up. In the middle of condensing OPD
2021-09-04 finished ripping appart the functional chunks
2021-09-28 pulled the Octavo appart some more and placed it where I think it fits best
2022-01-30 KiCad Port of oresat live card v1.1
2022-02-27 BOM and minor cosmetic schematic updates
2022-04-30 Board updates for V1.2, more routing. Design review 1
2022-05-01 Initial import of Eagle files to KiCad
2022-05-01 re importing eagle files to kicad
2022-05-04 Deleting redundant files
2022-05-09 OreSat Live card V1.2, last silkscreen tweaks and edgecut fixes
2022-05-13 Added kicad temp files to .gitignore, and removed committed temp files.
2022-05-29 Revert "OreSatLive Card v1.2, schematic changes that I totally ment to not push last time I swear that was totally intentional"
    This reverts commit 8d63213ca5702f650b1cf534c3d24906942b58ae.
2022-05-30 Shifted C75 to be out of the way of the lens
2022-05-31 Reverted SMPM pocket drills to be outlines
2022-05-31 Fixed issue with priority level of ground plane polygon.
2022-06-17 Pushed new BOM with backup PNs, removed deprecated Eagle files, added pdf schematics
2022-07-06 Fixed schematic error with 5v regulators
2022-07-19 restoring deleted Eagle v1.1 files
2022-07-19 fixed microstrip soldermask pull keepaway
2022-07-19 fixed u.fl pad missing gnd connection
2022-07-20 cleaned up DRC errors
2022-09-18 Fixed a few DRC errors
2022-09-20 Got most of the the DRC errors, started cleaning up the warnings
2022-10-06 changes L1 and L2 to coilcraft XGL4020, grounded pin 8 of U11 for alt part compatability
2022-10-26 replaced smpm footprint, added stitching around smpm
2022-10-26 fixed more DRC errors
2022-10-29 implamented some of the changes discussed with Andrew
2022-10-31 I think this might have actully been what my last commit should have been
2022-11-03 removed weird splig ground plane
2022-11-21 generated ibom
2023-12-21 Updated OreSat Live Card. Added changes from the C3 v6 Octavo circuitry and GPS card update. Fixed some GitHub issues. Board layout still in progress.
2024-01-02 Updated silk screen and small schematic changes
2024-01-02 Fixed issue with VPD diodes
2024-01-02 Cleaned up ERC and DRC errors on DxWiFi Card
2024-05-12 Upgraded to KiCAD 8.0. Added notes on U.FL cable and USB cables to wifi and camera.
2024-07-11 Create oresat_live_receive
    Receive section for TX/RX board
2024-07-12 updated symbol paths to oresat libraries and created pcb file
2024-07-18 Created PCB and started arranging components on receive path card
2024-07-21 added DPNs to BOM
2024-08-15 simple text changes
2024-08-15 Updated board layout, traces widths, and silkscreen
2024-08-19 5V path changes and silkscreen descriptors update
2024-09-01 Updated silkscreen, grounding, and Ref Des alignment
2024-09-05 fixed connector reference designators and BOM for receive test board
2024-09-09 Added RF Tools trace
2024-09-18 refixing changes from design review
2024-09-19 added missing DPN and MPN, fixed silkscreen labels
2025-04-05 added new sheets for LNA and switching
2025-04-26 completed LNA minus pwr detect.
2025-05-03 added RF scwitches
2025-05-10 implemented notes from Oliver. Added notes for self to fix later
2025-05-23 implemented notes form Oliver J
2025-07-06 updated sheet numbering and title, merged antenna switching and tx rx switching sheets
2025-07-06 removed unused tx_rx flag
2025-08-02 Changed C118, R124, R125 from 0603 to 0402, starting layout and routing
2025-08-05 swapped placement of R105 and R88, changed R109 from 100 to 56 ohms, relabelled PWR_DET_OUT to RX_DET_OUT, added inverter to TX/RX Control switch and swapped RF1 and RF2
2025-08-23 initial routing pass completed, moved R144 and R155 to output of U6.
2025-09-17 Fixed schematic symbolrs, add notes about control logic, fixed RF path and teardrops, removed 1.1V power LED
2025-09-17 Cleaning up respository, consistent naming, and removing old cruft.
2025-09-17 Rename files to be consistent with other octavo designs.
2025-09-17 Updated OPD / power page and synced with CFC processor, fixed layout issues.
2025-09-17 Updated SIP A, B, and C. Lots of cleanup of crazy routing - this board is long in the tooth and has been rerouted several times, so there's a lot of crazy routing. Cleaning up a bit is really helping.
2025-09-21 Some changes from Oliver
2025-09-21 add GND vias near PA
2025-09-22 Moved WiFi switch to 5VA, making the entire RF subsystem powered off that one supply. Fixed up RF path, still need to remove solder mask.
2025-10-29 added Olivers BOM and footprint changes, cleaned up pcb
2025-11-02 Added f.mask to all RF traces
2025-12-23 added 100p cap to U34 CTRL line, some BOM changes
2026-05-21 Added latest BOM changes
2026-06-28 Component update
    Updated the footprint for EEPROM connector
